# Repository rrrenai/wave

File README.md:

# ~ wave ~
*wave* is an attempt to revolutionize the head phone listening experience. If you know me irl, you'll know that I easily lose focus when people talk to me and I proactively believe I am going deaf. *wave* attempts to fix this issue by serving a a directional source selector for incoming sounds, eliminating distractions from environmental noise. 

These headphones utilize an FPGA, I2S MEMS microphones, and scrap headphone drivers. The FPGA and RPI work in tandem to collect and process incoming signals real time, seamlessly upgrading the listening experience.

The headphones have 2 half PCBs, which are connected via 3 JST cables. It collects audio data through 8 ICS-520000 MEMS microphones, connected together via TDM and parsed directly on the FPGA. The data is then quickly ran through a reduced TF-Gridnet DNN, where the target speaker is isolated and played back to the user.

# Schematic

# BOM
| Item                        |   Price                           | Quantity |  Subtotal                                    |
|-----------------------------|-----------------------------------|----------|----------------------------------------------|
| Ear cup / case              |  $              10.00             | 1        |  $                             10.00         |
| Head band                   |  $                       10.00    | 1        |  $                             10.00         |
| Bluetooth                   |  $                          1.79  | 1        |  $                               1.79        |
| Aliexpress shipping         |  $                6.63            | 1        |  $                               6.63        |
| Aliexpress tax              |  $                4.42            | 1        |  $                               4.42        |
| Cushion / seal material     |  $                5.26            | 2        |  $                             10.52         |
| LiPo                        |  $                4.95            | 2        |  $                               9.90        |
| Sound amp                   |  $                1.26            | 1        |  $                               1.26        |
| Charge Protection IC        |  $                1.99            | 1        |  $                               1.99        |
| Tang Nano 9k                |  $              18.17             | 1        |  $                             18.17         |
| Amazon Shipping / Handling  |  $              12.98             | 1        |  $                             12.98         |
| Amazon Estimated Tax        |  $                9.11            | 1        |  $                               9.11        |
| Audio driver for headphones |  $                       10.69    | 2        |  $                             21.38         |
| Digikey Shipping            |  $                6.99            | 1        |  $                               6.99        |
| Digikey Tarriff             |  $                2.14            | 1        |  $                               2.14        |
| Ebay shipping               |  $                4.95            | 1        |  $                               4.95        |
| Ebay tax                    |  $                0.64            | 1        |  $                               0.64        |
| Buttons                     |  $                          5.00  | 4        |  $                             20.00         |
| LED                         |  $                    -           | 2        |  $                                      -    |
| PCB (L + R)                 |  $                8.27            | 1        |  $                               8.27        |
| I2S Microphones             |  $                2.84            | 10       |  $                             28.40         |
| Mouser shipping             |  $                7.99            | 1        |  $                               7.99        |
| TOTAL                       |                                   |          |  $                          197.53           |

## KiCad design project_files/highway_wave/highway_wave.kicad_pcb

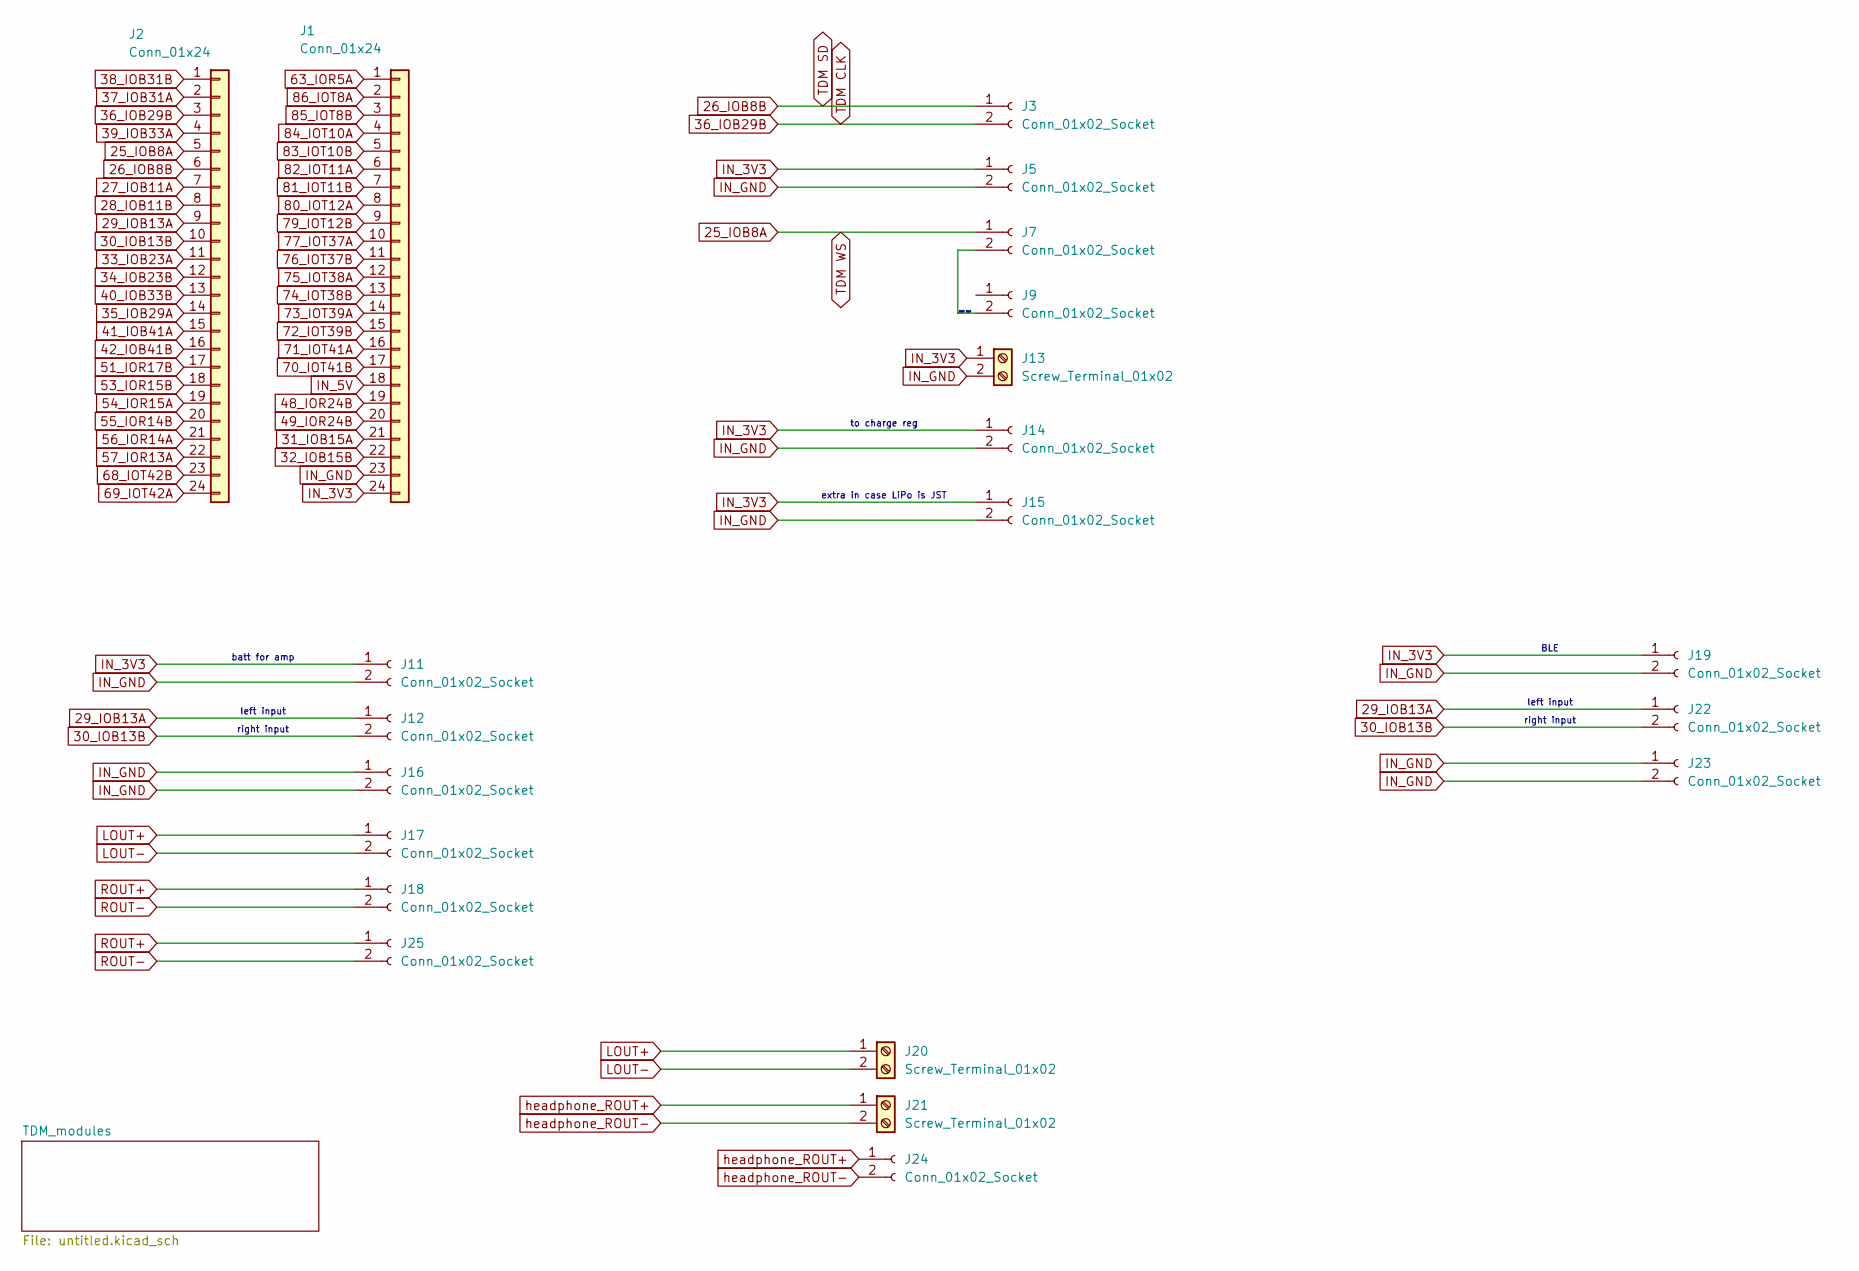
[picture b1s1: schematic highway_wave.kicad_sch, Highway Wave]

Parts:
J1, J2: Conn_01x24; PinSocket_1x24_P2.54mm_Vertical
J3, J5, J7, J9, J11, J12, J14, J15, J16, J17, J18, J19, J22, J23, J24, J25: Conn_01x02_Socket; JST_PH_B2B-PH-K_1x02_P2.00mm_Vertical
J13, J20, J21: Screw_Terminal_01x02; TerminalBlock_MetzConnect_Type101_RT01602HBWC_1x02_P5.08mm_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

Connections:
25_IOB8A: J2.5, J7.1
26_IOB8B: J2.6, J3.1; also elsewhere on the board
27_IOB11A: J2.7
28_IOB11B: J2.8
29_IOB13A: J2.9, J12.1, J22.1
30_IOB13B: J2.10, J12.2, J22.2
31_IOB15A: J1.21
32_IOB15B: J1.22
33_IOB23A: J2.11
34_IOB23B: J2.12
35_IOB29A: J2.14
36_IOB29B: J2.3, J3.2; also elsewhere on the board
37_IOB31A: J2.2
38_IOB31B: J2.1
39_IOB33A: J2.4
40_IOB33B: J2.13
41_IOB41A: J2.15
42_IOB41B: J2.16
48_IOR24B: J1.19
49_IOR24B: J1.20
51_IOR17B: J2.17
53_IOR15B: J2.18
54_IOR15A: J2.19
55_IOR14B: J2.20
56_IOR14A: J2.21
57_IOR13A: J2.22
63_IOR5A: J1.1
68_IOT42B: J2.23
69_IOT42A: J2.24
70_IOT41B: J1.17
71_IOT41A: J1.16
72_IOT39B: J1.15
73_IOT39A: J1.14
74_IOT38B: J1.13
75_IOT38A: J1.12
76_IOT37B: J1.11
77_IOT37A: J1.10
79_IOT12B: J1.9
80_IOT12A: J1.8
81_IOT11B: J1.7
82_IOT11A: J1.6
83_IOT10B: J1.5
84_IOT10A: J1.4
85_IOT8B: J1.3
86_IOT8A: J1.2
IN_3V3: J1.24, J5.1, J11.1, J13.1, J14.1, J15.1, J19.1; also elsewhere on the board
IN_5V: J1.18
IN_GND: J1.23, J5.2, J11.2, J13.2, J14.2, J15.2, J16.1, J16.2, J19.2, J23.1, J23.2; also elsewhere on the board
LOUT+: J17.1, J20.1
LOUT-: J17.2, J20.2
unnamed: J7.2, J9.2
ROUT+: J18.1, J25.1
ROUT-: J18.2, J25.2
headphone_ROUT+: J21.1, J24.1
headphone_ROUT-: J21.2, J24.2

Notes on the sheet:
BLE
extra in case LiPo is JST
right input
left input
batt for amp
to charge reg
WSO Mk4

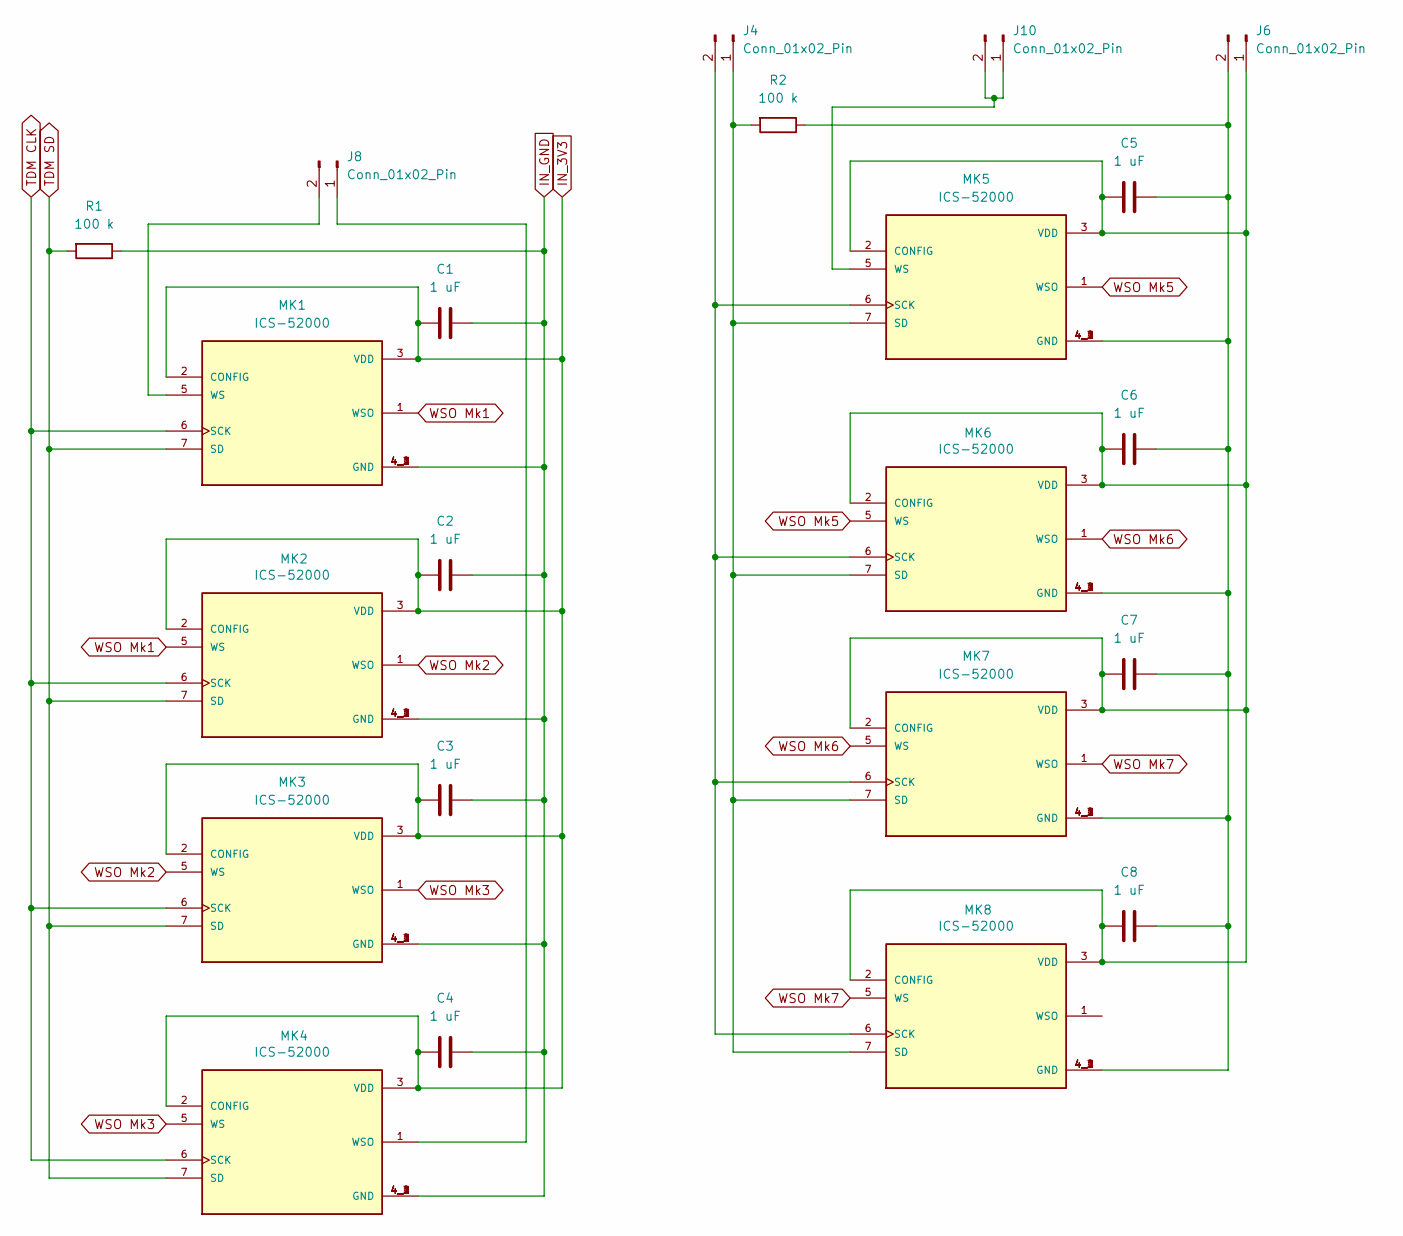
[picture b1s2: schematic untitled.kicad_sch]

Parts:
C1, C2, C3, C4, C5, C6, C7, C8: 1 uF; C_Disc_D5.0mm_W2.5mm_P5.00mm
J4, J6, J8, J10: Conn_01x02_Pin; JST_PH_B2B-PH-K_1x02_P2.00mm_Vertical
MK1, MK2, MK3, MK4, MK5, MK6, MK7, MK8: ICS-52000; MIC_ICS-52000; PARTREV 1.3
R1, R2: 100 k; R_Axial_DIN0207_L6.3mm_D2.5mm_P7.62mm_Horizontal

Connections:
26_IOB8B: MK1.7 (SD), MK2.7 (SD), MK3.7 (SD), MK4.7 (SD), R1.2; also elsewhere on the board
36_IOB29B: MK1.6 (SCK), MK2.6 (SCK), MK3.6 (SCK), MK4.6 (SCK); also elsewhere on the board
IN_3V3: C1.1, C2.1, C3.1, C4.1, MK1.2 (CONFIG), MK1.3 (VDD), MK2.2 (CONFIG), MK2.3 (VDD), MK3.2 (CONFIG), MK3.3 (VDD), MK4.2 (CONFIG), MK4.3 (VDD); also elsewhere on the board
IN_GND: C1.2, C2.2, C3.2, C4.2, MK1.4_1 (GND), MK1.4_2 (GND), MK1.4_3 (GND), MK1.4_4 (GND), MK2.4_1 (GND), MK2.4_2 (GND), MK2.4_3 (GND), MK2.4_4 (GND), MK3.4_1 (GND), MK3.4_2 (GND), MK3.4_3 (GND), MK3.4_4 (GND), MK4.4_1 (GND), MK4.4_2 (GND), MK4.4_3 (GND), MK4.4_4 (GND), R1.1; also elsewhere on the board
unnamed: J4.1, MK5.7 (SD), MK6.7 (SD), MK7.7 (SD), MK8.7 (SD), R2.2
unnamed: J4.2, MK5.6 (SCK), MK6.6 (SCK), MK7.6 (SCK), MK8.6 (SCK)
unnamed: C5.1, C6.1, C7.1, C8.1, J6.1, MK5.2 (CONFIG), MK5.3 (VDD), MK6.2 (CONFIG), MK6.3 (VDD), MK7.2 (CONFIG), MK7.3 (VDD), MK8.2 (CONFIG), MK8.3 (VDD)
unnamed: C5.2, C6.2, C7.2, C8.2, J6.2, MK5.4_1 (GND), MK5.4_2 (GND), MK5.4_3 (GND), MK5.4_4 (GND), MK6.4_1 (GND), MK6.4_2 (GND), MK6.4_3 (GND), MK6.4_4 (GND), MK7.4_1 (GND), MK7.4_2 (GND), MK7.4_3 (GND), MK7.4_4 (GND), MK8.4_1 (GND), MK8.4_2 (GND), MK8.4_3 (GND), MK8.4_4 (GND), R2.1
unnamed: J8.1, MK4.1 (WSO)
unnamed: J8.2, MK1.5 (WS)
unnamed: J10.1, J10.2, MK5.5 (WS)
WSO Mk1: MK1.1 (WSO), MK2.5 (WS)
WSO Mk2: MK2.1 (WSO), MK3.5 (WS)
WSO Mk3: MK3.1 (WSO), MK4.5 (WS)
WSO Mk5: MK5.1 (WSO), MK6.5 (WS)
WSO Mk6: MK6.1 (WSO), MK7.5 (WS)
WSO Mk7: MK7.1 (WSO), MK8.5 (WS)

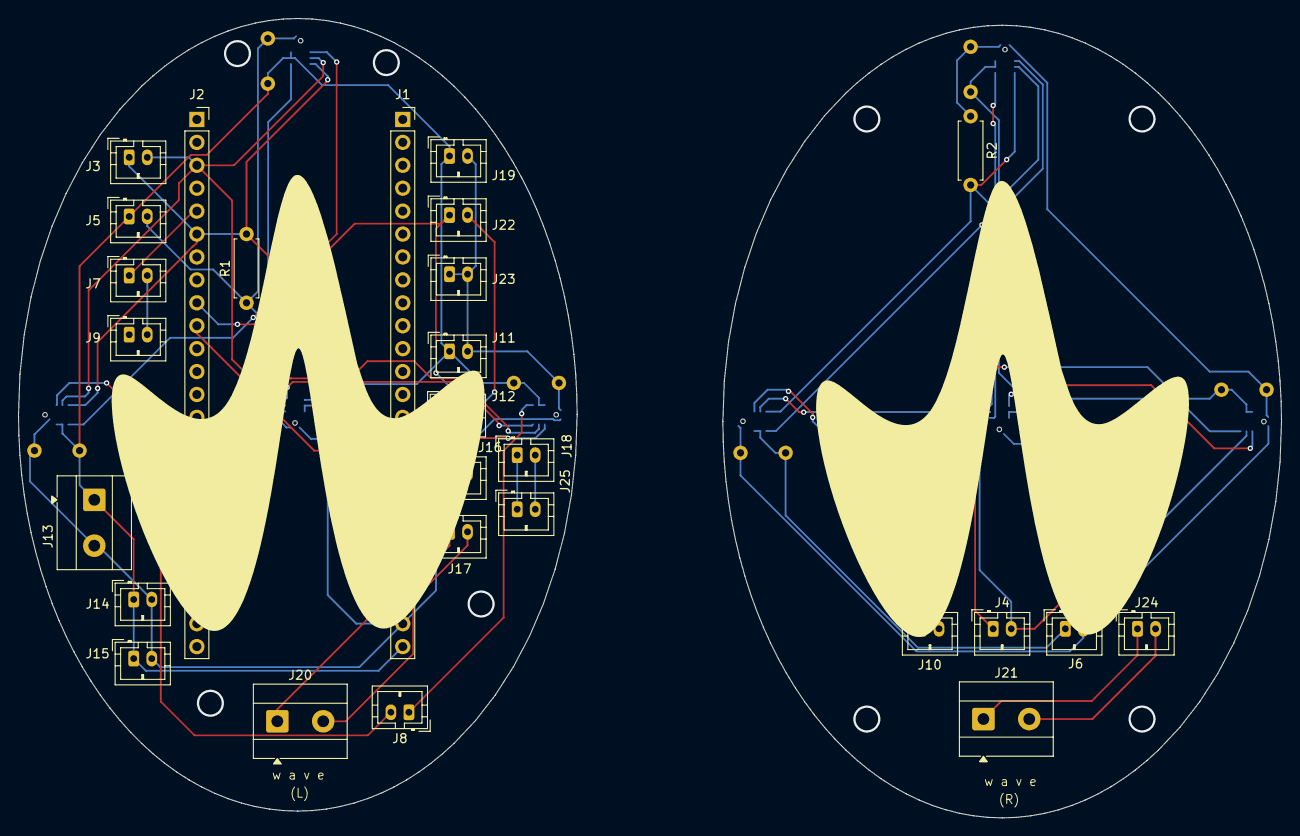
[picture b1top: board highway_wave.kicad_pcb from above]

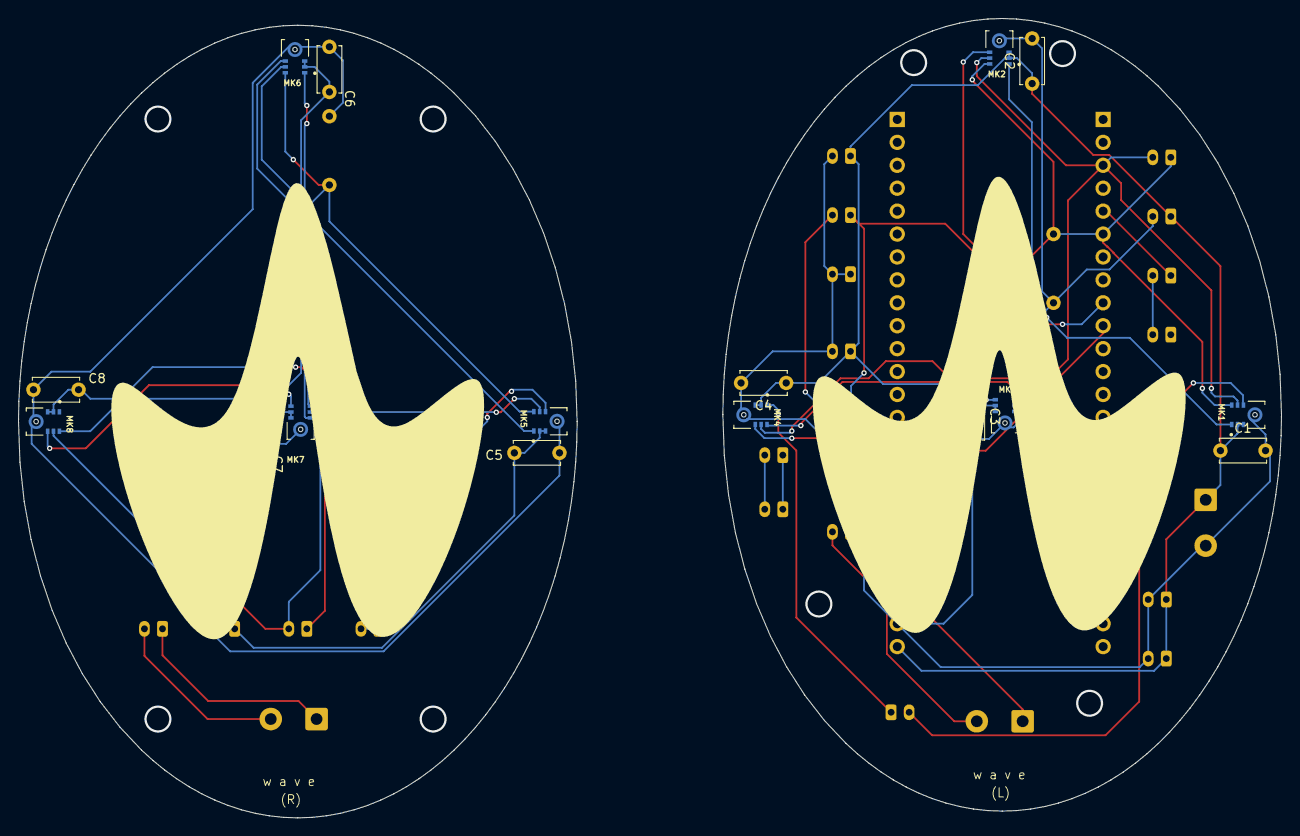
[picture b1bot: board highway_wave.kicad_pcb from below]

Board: 2 copper layers, 140.0 x 88.6 mm, 43 parts (16 on the bottom side), 27 nets.

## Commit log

2025-05-23 basic idea nothing conrete yet
2025-06-14 cad & readme
2025-06-14 create python and hdl files
2025-06-14 added schematic
2025-06-15 Added FPGA to parts list and correct driver
2025-06-20 finished schem
2025-06-20 exported schem
2025-06-20 final updated README
2025-06-23 ESP32-S3 direction
2025-06-26 big updates to pcb
2025-06-28 random committ
2025-07-11 fixed pcb
2025-07-11 journal updates
2025-07-11 ok final?
2025-07-11 new step file
2025-07-16 Updated BOM and ReadMe
2025-07-16 oops forgot to save the xlsx
2025-07-19 fixed math on journal.md
2025-07-28 moved caps on PCB
2025-07-28 Total hours is 34.5
2025-08-03 update BOM
2025-08-03 update csv
2026-01-06 push
